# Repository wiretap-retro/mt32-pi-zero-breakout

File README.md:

# mt32-pi Zero Breakout
A small breakout board for custom mt32-pi projects using a Raspberry Pi Zero 2 W. 
\
\

## Info
The core project design is attributed to Dale Whinham and his awesome mt32-pi project. Repo link: https://github.com/dwhinham/mt32-pi
\
\
This PCB I designed is a breakout board style header for small DIY mt32-pi projects. There are no clunky headers or connectors to take up extra space. It allows for low clearance if you direct solder as many components as you can. 
\
\
I have included the full KiCad project along with the Mouser Cart, BOM, and Gerber files for ease of upload. The design is minimalist to allow you flexibility for connectivity. I plan on using this with mostly panel-mount style connectors in my enclosure, so all I needed was solder points or 2.54mm spacing dupont connectors for everything.
\
\
Designed for use with my 5.25" bay panel found here: https://github.com/wiretap-retro/mt32-pi-bay

## Parts
The parts not listed in the BOM that you need are as follows:
- GY-PCM5102 Digital to Analog Audio Converter
- Raspberry Pi Zero 2 W
- Any other components for your specific project such as external buttons/encoders, external connectors, and i2c screens.

\
Please read the original mt32-pi repository linked in the information section for compatible screens, encoders, etc..

## Revision Notes
2025-05-03 --- Updated BOM to correct capacitor C1 diameter/size.

## License
This project uses the UNLICENSE. Feel free to do what you want with it. Check over the project before ordering. Build at your own risk.

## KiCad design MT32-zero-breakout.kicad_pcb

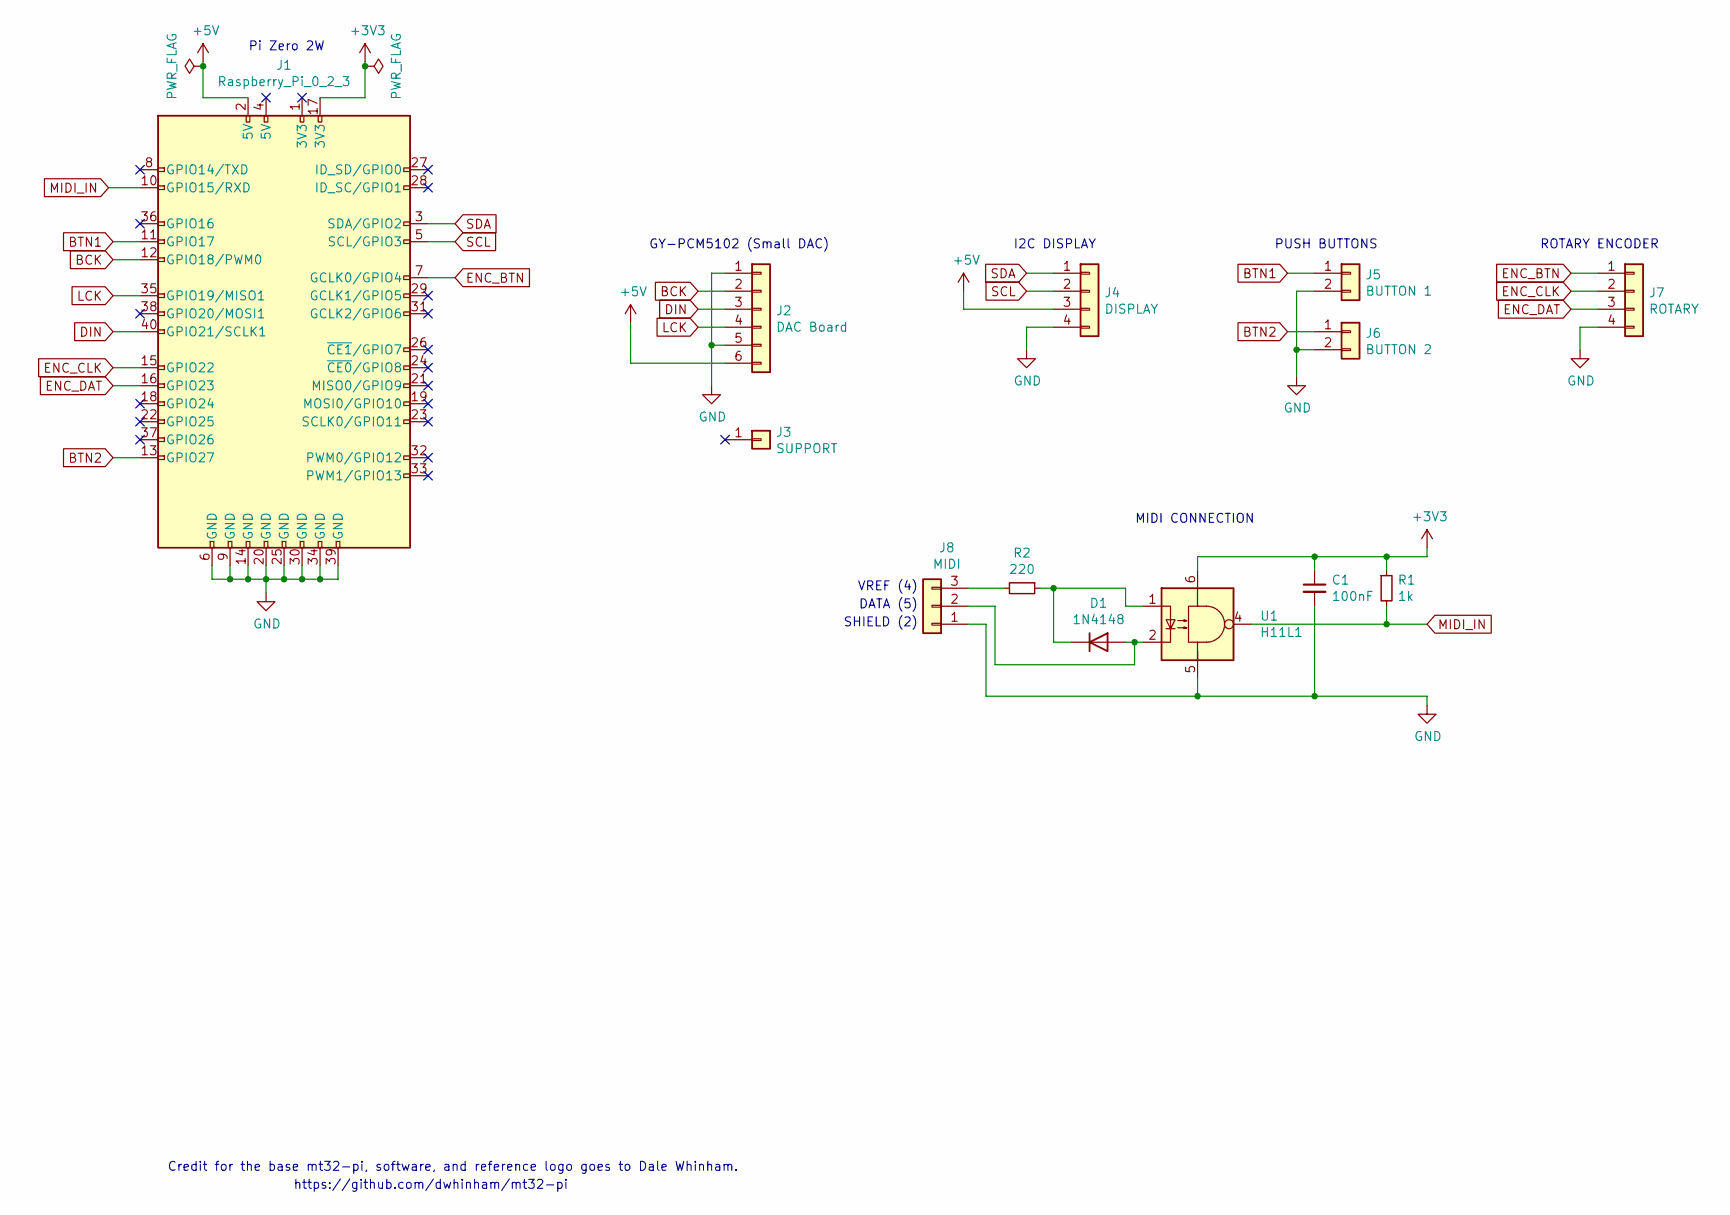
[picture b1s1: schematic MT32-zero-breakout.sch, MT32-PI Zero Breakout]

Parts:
C1: 100nF; C_Disc_D9.0mm_W2.5mm_P5.00mm; Part No. 565R20GAP10
D1: 1N4148; D_DO-35_SOD27_P7.62mm_Horizontal
J1: Raspberry_Pi_0_2_3; PinHeader_2x20_P2.54mm_Vertical
J2: DAC Board; PinHeader_1x06_P2.54mm_Vertical
J3: SUPPORT; PinHeader_1x01_P2.54mm_Vertical
J4: DISPLAY; PinHeader_1x04_P2.54mm_Vertical
J5: BUTTON 1; PinHeader_1x02_P2.54mm_Vertical
J6: BUTTON 2; PinHeader_1x02_P2.54mm_Vertical
J7: ROTARY; PinHeader_1x04_P2.54mm_Vertical
J8: MIDI; PinHeader_1x03_P2.54mm_Vertical
R1: 1k; R_Axial_DIN0207_L6.3mm_D2.5mm_P7.62mm_Horizontal
R2: 220; R_Axial_DIN0207_L6.3mm_D2.5mm_P7.62mm_Horizontal
U1: H11L1; DIP-6_W7.62mm

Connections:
+3V3: C1.1, J1.17 (3V3), R1.1, U1.6
+5V: J1.2 (5V), J2.6, J4.3
BCK: J1.12 (GPIO18/PWM0), J2.2
BTN1: J1.11 (GPIO17), J5.1
BTN2: J1.13 (GPIO27), J6.1
DIN: J1.40 (GPIO21/SCLK1), J2.3
ENC_BTN: J1.7 (GCLK0/GPIO4), J7.1
ENC_CLK: J1.15 (GPIO22), J7.2
ENC_DAT: J1.16 (GPIO23), J7.3
GND: C1.2, J1.6 (GND), J1.9 (GND), J1.14 (GND), J1.20 (GND), J1.25 (GND), J1.30 (GND), J1.34 (GND), J1.39 (GND), J2.1, J2.5, J4.4, J5.2, J6.2, J7.4, J8.1, U1.5
LCK: J1.35 (GPIO19/MISO1), J2.4
MIDI_IN: J1.10 (GPIO15/RXD), R1.2, U1.4
unnamed: D1.1 (K), R2.1, U1.1
unnamed: D1.2 (A), J8.2, U1.2
unnamed: J8.3, R2.2
SCL: J1.5 (SCL/GPIO3), J4.2
SDA: J1.3 (SDA/GPIO2), J4.1

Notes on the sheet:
Pi Zero 2W
GY-PCM5102 (Small DAC)
I2C DISPLAY
PUSH BUTTONS
ROTARY ENCODER
SHIELD (2)
DATA (5)
VREF (4)
MIDI CONNECTION
https://github.com/dwhinham/mt32-pi
Credit for the base mt32-pi, software, and reference logo goes to Dale Whinham.

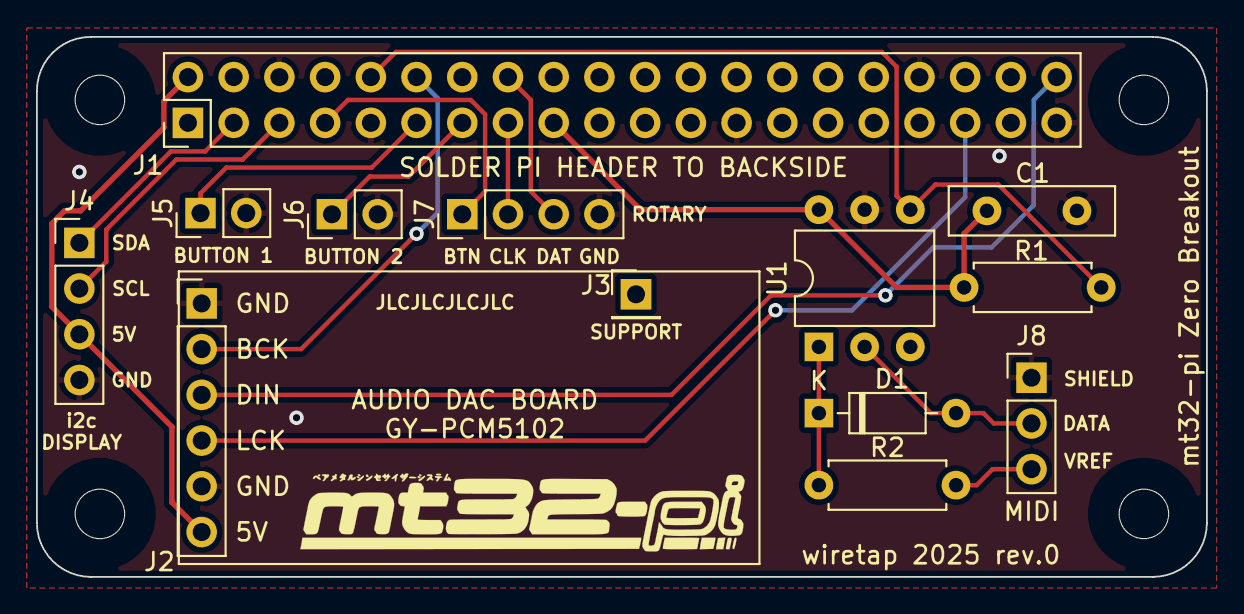
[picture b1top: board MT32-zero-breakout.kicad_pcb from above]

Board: 2 copper layers, 65.0 x 30.0 mm, 13 parts (0 on the bottom side), 17 nets.

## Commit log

2025-04-15 Create LICENSE
2025-05-03 Update BOM
    Updated BOM to correct capacitor diameter/size.
